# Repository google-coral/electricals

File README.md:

# Electricals for Coral.ai projects

This repo contains schematics and other pieces of electrical designs for coral.ai projects

## Support

If you have question, comments or requests concerning this library, please
reach out to coral-support@google.com.

## License

[Apache License 2.0](LICENSE)

## Warning

The designs are provided as is, the user assumes any and all risk if utilizing
the designs contained here. Google takes no responsibility for the consequences
of manufacturing, deploying and/or using the product of these designs.

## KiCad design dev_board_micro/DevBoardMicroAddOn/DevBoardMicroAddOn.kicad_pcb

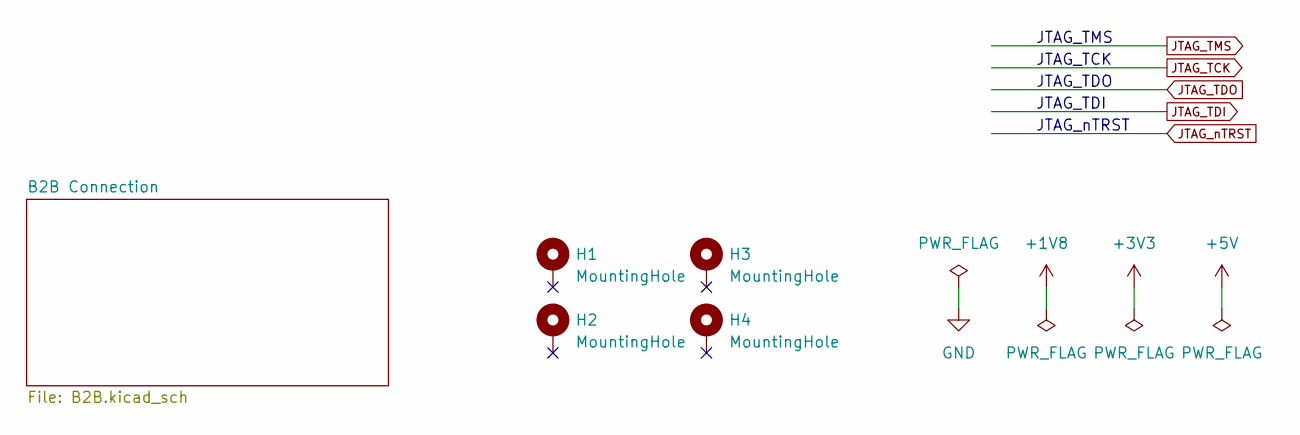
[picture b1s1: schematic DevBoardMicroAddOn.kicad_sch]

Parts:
H1, H2, H3, H4: MountingHole; 9774030951R

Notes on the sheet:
JTAG_TCK
JTAG_nTRST
JTAG_TMS
JTAG_TDO
JTAG_TDI

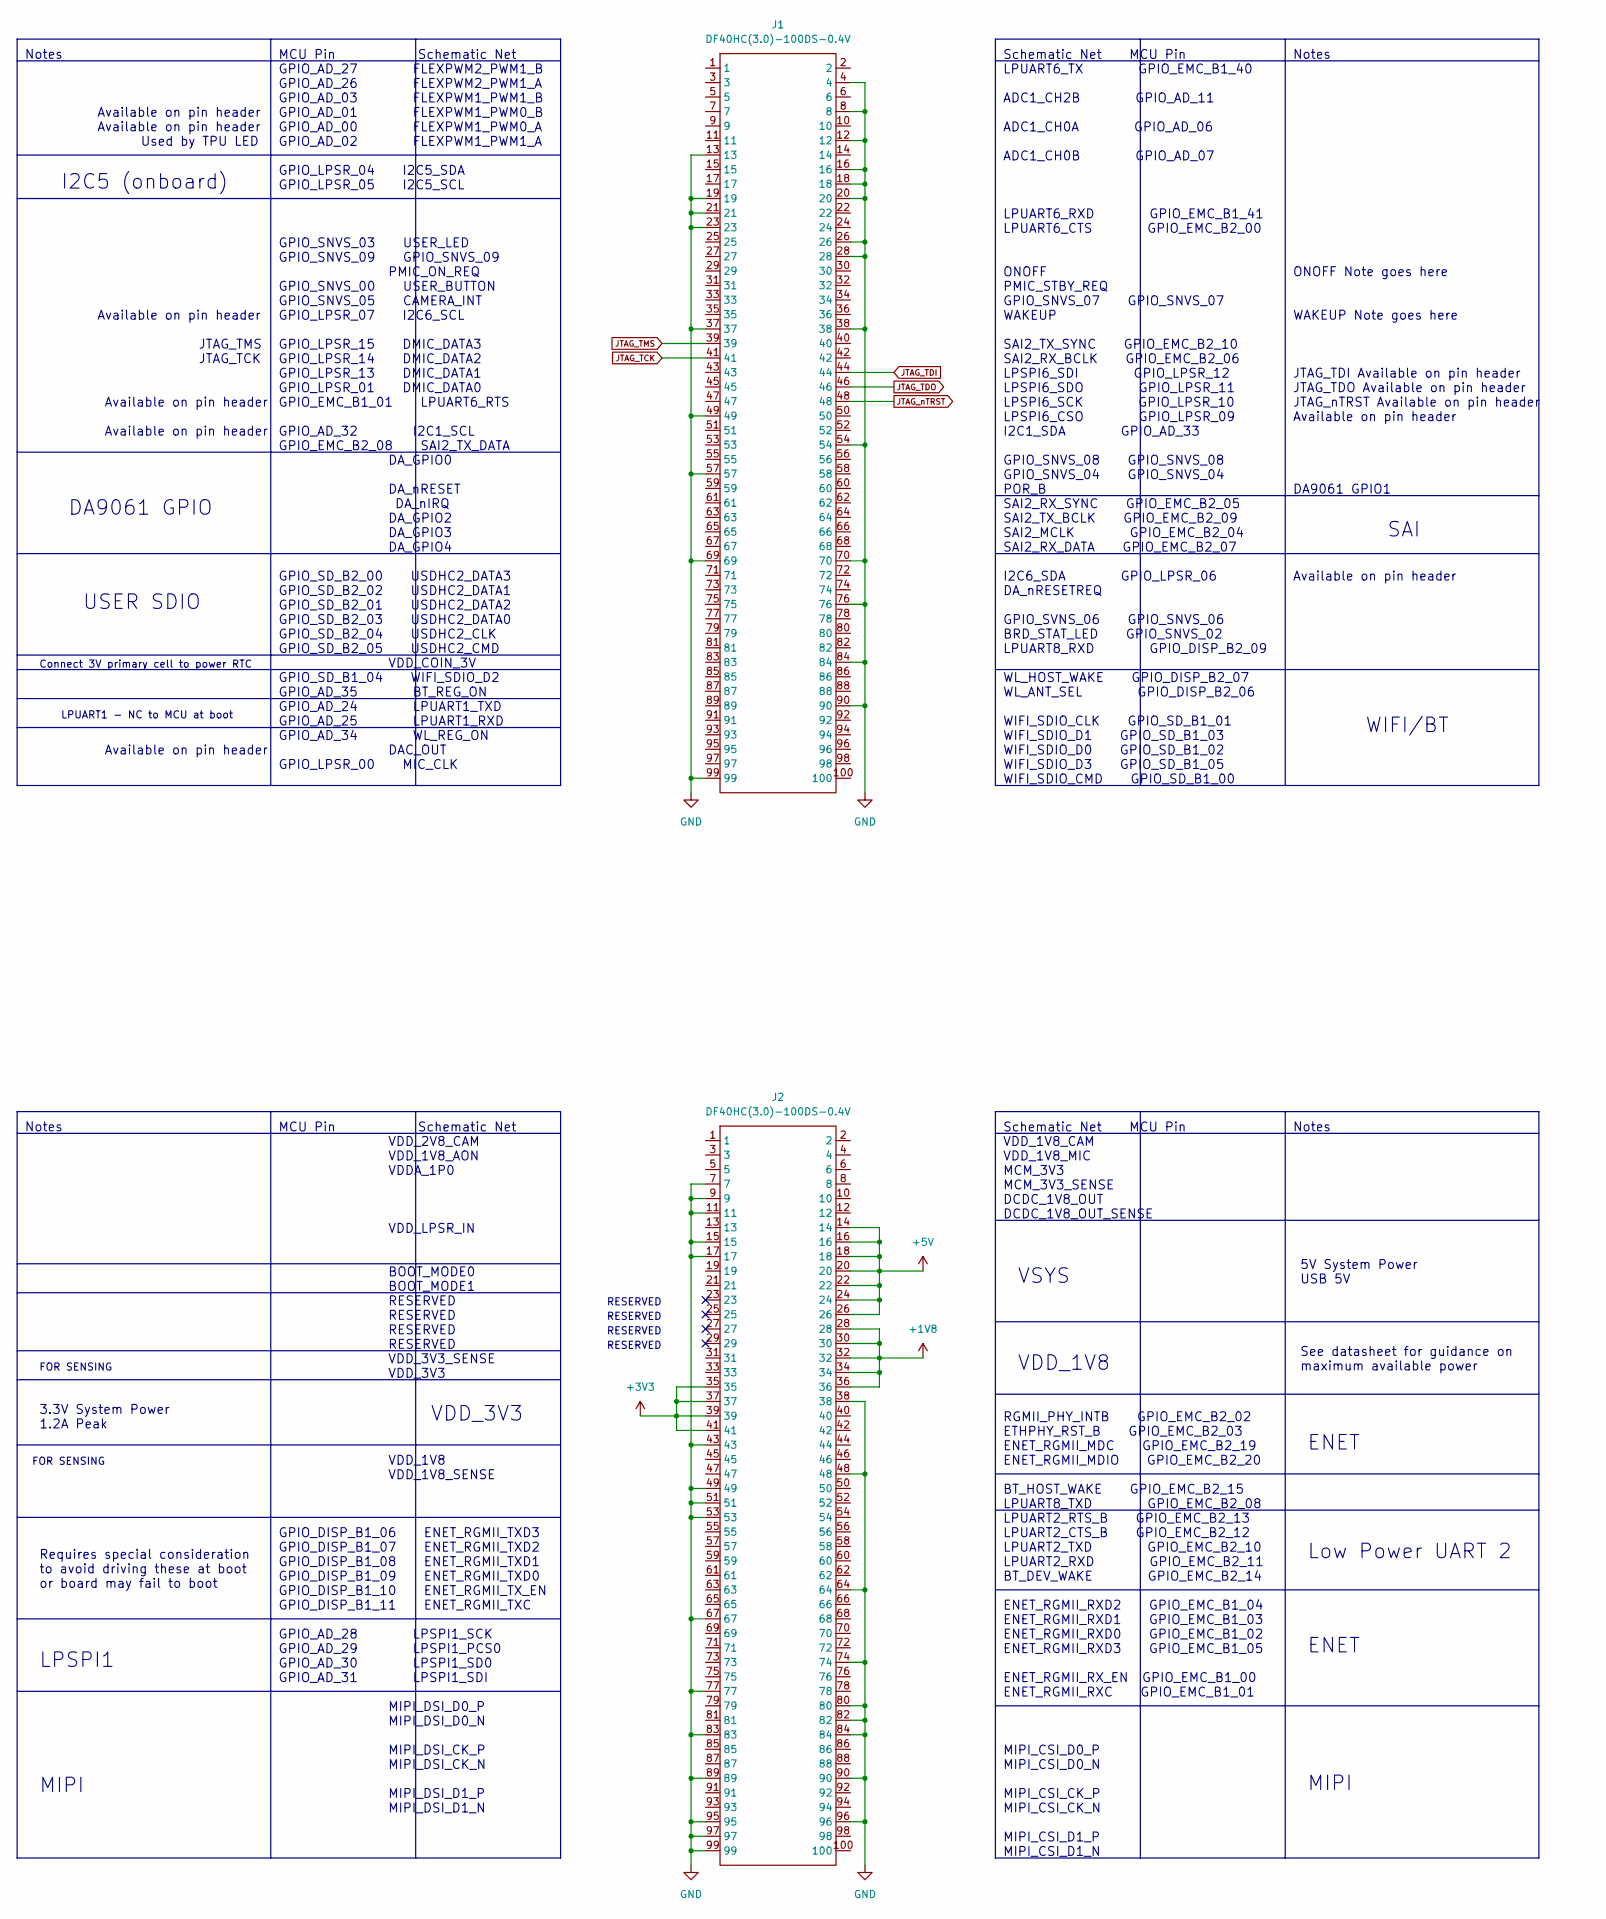
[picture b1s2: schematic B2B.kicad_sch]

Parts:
J1, J2: DF40HC(3.0)-100DS-0.4V; DF40HC_3.0-100DS-0.4V

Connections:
+1V8: J2.28, J2.30, J2.32, J2.34, J2.36
+3V3: J2.35, J2.37, J2.39, J2.41
+5V: J2.14, J2.16, J2.18, J2.20, J2.22, J2.24, J2.26
GND: J1.4, J1.8, J1.12, J1.13, J1.16, J1.18, J1.19, J1.20, J1.21, J1.23, J1.26, J1.28, J1.37, J1.38, J1.49, J1.54, J1.57, J1.69, J1.70, J1.76, J1.84, J1.90, J1.99, J2.7, J2.9, J2.11, J2.15, J2.17, J2.38, J2.43, J2.48, J2.49, J2.51, J2.53, J2.64, J2.67, J2.74, J2.77, J2.80, J2.82, J2.83, J2.84, J2.89, J2.90, J2.95, J2.96, J2.97, J2.99
JTAG_TCK: J1.41
JTAG_TDI: J1.44
JTAG_TDO: J1.46
JTAG_TMS: J1.39
JTAG_nTRST: J1.48

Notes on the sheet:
SAI
VDD_3V3
MCU Pin Schematic Net VDD_2V8_CAM VDD_1V8_AON VDDA_1P0 VDD_LPSR_IN BOOT_MODE0 BOOT_MODE1 RESERVED RESERVED RESERVED RESERVED VDD_3V3_SENSE VDD_3V3 VDD_1V8 VDD_1V8_SENSE GPIO_DISP_B1_06 ENET_RGMII_TXD3 GPIO_DISP_B1_07 ENET_RGMII_TXD2 GPIO_DISP_B1_08 ENET_RGMII_TXD1 GPIO_DISP_B1_09 ENET_RGMII_TXD0 GP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
WAKEUP Note goes here
Schematic Net MCU Pin VDD_1V8_CAM VDD_1V8_MIC MCM_3V3 MCM_3V3_SENSE DCDC_1V8_OUT DCDC_1V8_OUT_SENSE RGMII_PHY_INTB GPIO_EMC_B2_02 ETHPHY_RST_B GPIO_EMC_B2_03 ENET_RGMII_MDC GPIO_EMC_B2_19 ENET_RGMII_MDIO GPIO_EMC_B2_20 BT_HOST_WAKE GPIO_EMC_B2_15 LPUART8_TXD GPIO_EMC_B2_08 LPUART2_RTS_B GPIO_EMC_B2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
LPSPI1
RESERVED
JTAG_nTRST Available on pin header
DA9061 GPIO
JTAG_TDI Available on pin header
Schematic Net MCU Pin LPUART6_TX GPIO_EMC_B1_40 ADC1_CH2B GPIO_AD_11 ADC1_CH0A GPIO_AD_06 ADC1_CH0B GPIO_AD_07 LPUART6_RXD GPIO_EMC_B1_41 LPUART6_CTS GPIO_EMC_B2_00 ONOFF PMIC_STBY_REQ GPIO_SNVS_07 GPIO_SNVS_07 WAKEUP SAI2_TX_SYNC GPIO_EMC_B2_10 SAI2_RX_BCLK GPIO_EMC_B2_06 LPSPI6_SDI GPIO_LPSR_12 L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
Notes
MIPI
Available on pin header
5V System Power USB 5V
3.3V System Power 1.2A Peak
DA9061 GPIO1
USER SDIO
See datasheet for guidance on maximum available power
MCU Pin Schematic Net GPIO_AD_27 FLEXPWM2_PWM1_B GPIO_AD_26 FLEXPWM2_PWM1_A GPIO_AD_03 FLEXPWM1_PWM1_B GPIO_AD_01 FLEXPWM1_PWM0_B GPIO_AD_00 FLEXPWM1_PWM0_A GPIO_AD_02 FLEXPWM1_PWM1_A GPIO_LPSR_04 I2C5_SDA GPIO_LPSR_05 I2C5_SCL GPIO_SNVS_03 USER_LED GPIO_SNVS_09 GPIO_SNVS_09 PMIC_ON_REQ GPIO_SNVS_0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
Connect 3V primary cell to power RTC
ENET
WIFI/BT
Requires special consideration to avoid driving these at boot or board may fail to boot
JTAG_TMS
ONOFF Note goes here
Used by TPU LED
FOR SENSING
I2C5 (onboard)
VDD_1V8
LPUART1 - NC to MCU at boot
JTAG_TCK
VSYS
JTAG_TDO Available on pin header
Low Power UART 2

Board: 2 copper layers, 6 parts (0 on the bottom side), 4 nets, no tracks yet.

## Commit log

2021-01-10 Schematics and layout for Coral Dev Board and Dev Board Mini
2022-10-05 Schematics and layout for Coral Dev Board Micro
